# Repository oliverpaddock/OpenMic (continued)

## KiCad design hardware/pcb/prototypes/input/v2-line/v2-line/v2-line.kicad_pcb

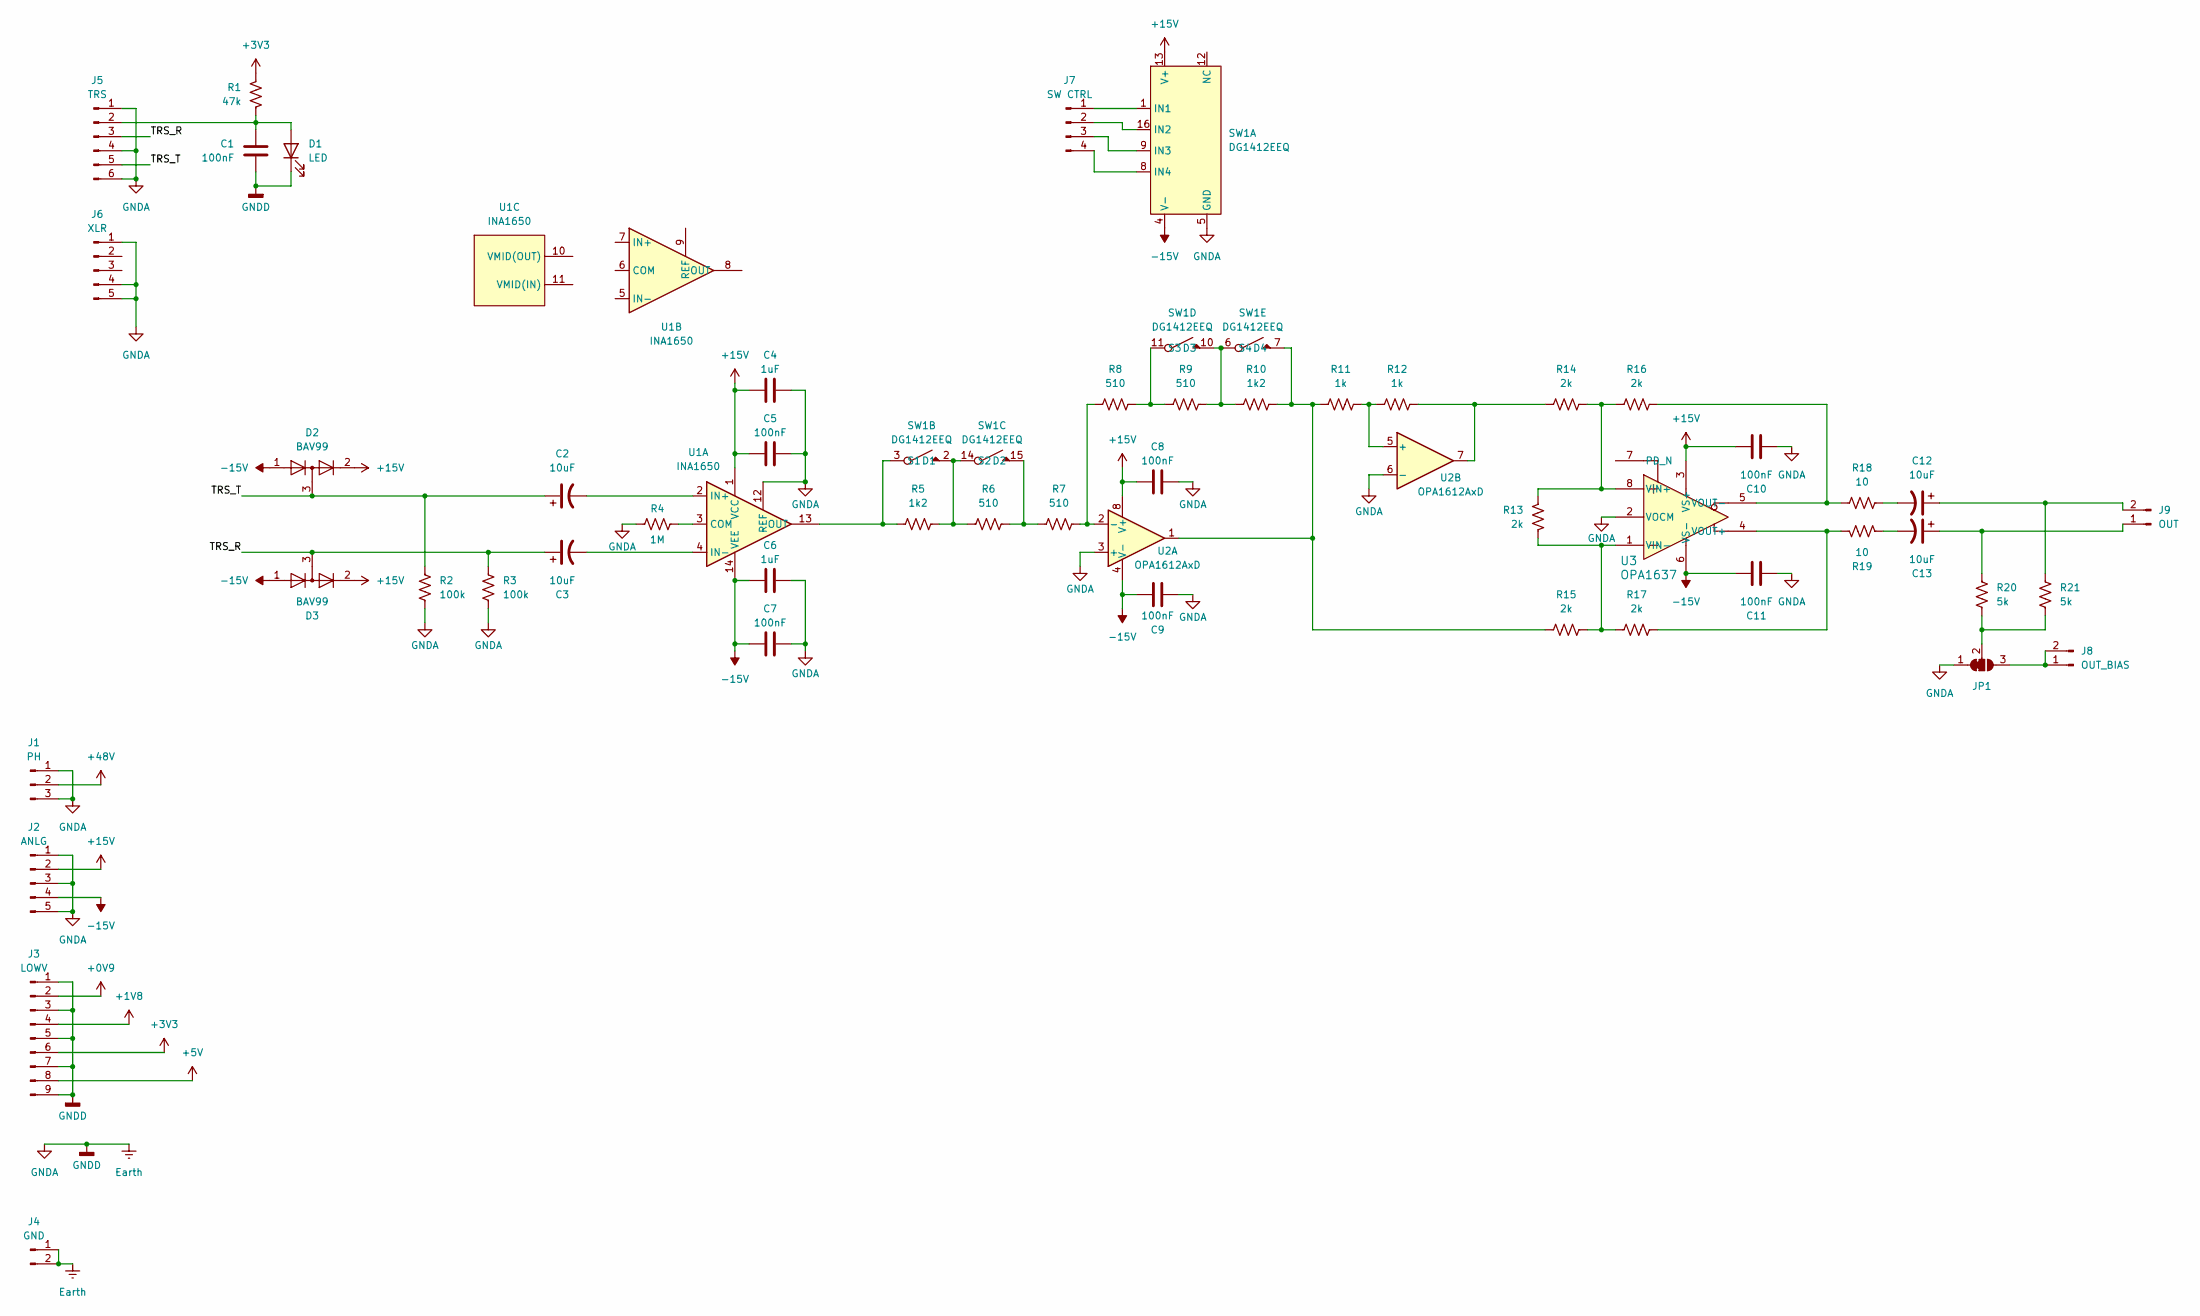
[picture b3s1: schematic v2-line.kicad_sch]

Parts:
C1, C10, C11: 100nF; C_0805_2012Metric_Pad1.18x1.45mm_HandSolder; Voltage 6
C2, C3, C12, C13: 10uF; C_Radial_D5.0mm_H11.0mm_P2.00mm; Voltage 50
C4, C6: 1uF; C_0805_2012Metric_Pad1.18x1.45mm_HandSolder; Voltage 50
C5, C7, C8, C9: 100nF; C_0805_2012Metric_Pad1.18x1.45mm_HandSolder; Voltage 50
D1: LED; LED_0805_2012Metric_Pad1.15x1.40mm_HandSolder
D2, D3: BAV99; SOT-23
J1: PH; PinHeader_1x03_P2.54mm_Vertical
J2: ANLG; PinHeader_1x05_P2.54mm_Vertical
J3: LOWV; PinHeader_1x09_P2.54mm_Vertical
J4: GND; PinHeader_1x02_P2.54mm_Vertical
J5: TRS; PinHeader_1x06_P2.54mm_Vertical
J6: XLR; PinHeader_1x05_P2.54mm_Vertical
J7: SW CTRL; PinHeader_1x04_P2.54mm_Vertical
J8: OUT_BIAS; PinHeader_1x02_P2.54mm_Vertical
J9: OUT; PinHeader_1x02_P2.54mm_Vertical
JP1: SolderJumper_3_Bridged12; SolderJumper-3_P1.3mm_Bridged12_RoundedPad1.0x1.5mm
R1: 47k; R_0805_2012Metric_Pad1.20x1.40mm_HandSolder
R2, R3: 100k; R_0805_2012Metric_Pad1.20x1.40mm_HandSolder
R4: 1M; R_0805_2012Metric_Pad1.20x1.40mm_HandSolder
R5, R10: 1k2; R_0805_2012Metric_Pad1.20x1.40mm_HandSolder
R6, R7, R8, R9: 510; R_0805_2012Metric_Pad1.20x1.40mm_HandSolder
R11, R12: 1k; R_0805_2012Metric_Pad1.20x1.40mm_HandSolder
R13, R14, R15, R16, R17: 2k; R_0805_2012Metric_Pad1.20x1.40mm_HandSolder
R18, R19: 10; R_0805_2012Metric_Pad1.20x1.40mm_HandSolder
R20, R21: 5k; R_0805_2012Metric_Pad1.20x1.40mm_HandSolder
SW1: DG1412EEQ; TSSOP-16_4.4x5mm_P0.65mm
U1: INA1650; TSSOP-14_4.4x5mm_P0.65mm
U2: OPA1612AxD; SOIC-8_3.9x4.9mm_P1.27mm
U3: OPA1637; VSSOP-8_3x3mm_P0.65mm

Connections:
+0V9: J3.2
+1V8: J3.4
+3V3: J3.6, R1.1
+5V: J3.8
+15V: C4.2, C5.2, C8.2, C10.1, D2.2 (A), D3.2 (A), J2.2, SW1.13 (V+), U1.1 (VCC), U2.8 (V+), U3.3 (VS+)
+48V: J1.2
-15V: C6.2, C7.2, C9.2, C11.1, D2.1 (K), D3.1 (K), J2.4, SW1.4 (V-), U1.14 (VEE), U2.4 (V-), U3.6 (VS-)
/TRS_R: C3.1, D3.3 (K), J5.3, R3.2
/TRS_T: C2.1, D2.3 (K), J5.5, R2.2
Earth: C1.2, C4.1, C5.1, C6.1, C7.1, C8.1, C9.1, C10.2, C11.2, D1.1 (K), J1.1, J1.3, J2.1, J2.3, J2.5, J3.1, J3.3, J3.5, J3.7, J3.9, J4.1, J4.2, J5.1, J5.4, J5.6, J6.1, J6.4, J6.5, JP1.1 (A), R2.1, R3.1, R4.1, SW1.5 (GND), U1.12 (REF), U2.3 (+), U2.6 (-), U3.2 (VOCM)
unnamed: C12.2, R18.2
unnamed: C13.2, R19.2
unnamed: C1.1, D1.2 (A), J5.2, R1.2
unnamed: J7.1, SW1.1 (IN1)
unnamed: J7.2, SW1.16 (IN2)
unnamed: J7.3, SW1.9 (IN3)
unnamed: J7.4, SW1.8 (IN4)
unnamed: J8.1, J8.2, JP1.3 (B)
unnamed: C13.1, J9.1, R20.2
unnamed: C12.1, J9.2, R21.2
unnamed: JP1.2 (C), R20.1, R21.1
unnamed: R12.1, R14.1, U2.7
unnamed: R5.1, R6.2, SW1.2 (D1), SW1.14 (S2)
unnamed: R5.2, SW1.3 (S1), U1.13 (OUT)
unnamed: R6.1, R7.2, SW1.15 (D2)
unnamed: R9.1, R10.2, SW1.6 (S4), SW1.10 (D3)
unnamed: R8.1, R9.2, SW1.11 (S3)
unnamed: R10.1, R11.2, R15.1, SW1.7 (D4), U2.1
unnamed: R4.2, U1.3 (COM)
unnamed: C2.2, U1.2 (IN+)
unnamed: C3.2, U1.4 (IN-)
unnamed: R7.1, R8.2, U2.2 (-)
unnamed: R11.1, R12.2, U2.5 (+)
unnamed: R13.2, R14.2, R16.1, U3.8 (VIN+)
unnamed: R13.1, R15.2, R17.1, U3.1 (VIN-)
unnamed: R17.2, R19.1, U3.4 (VOUT+)
unnamed: R16.2, R18.1, U3.5 (VOUT-)

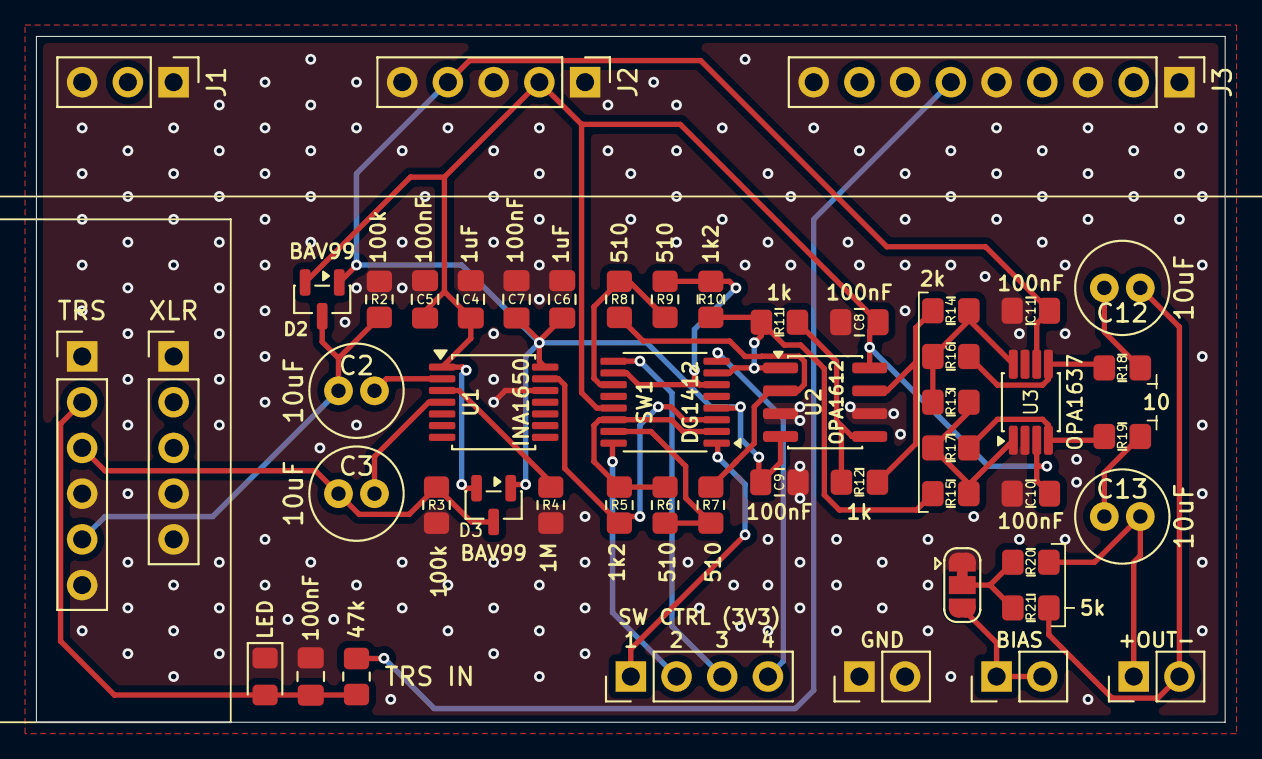
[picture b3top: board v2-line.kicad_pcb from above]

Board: 2 copper layers, 66.0 x 38.1 mm, 51 parts (0 on the bottom side), 33 nets.

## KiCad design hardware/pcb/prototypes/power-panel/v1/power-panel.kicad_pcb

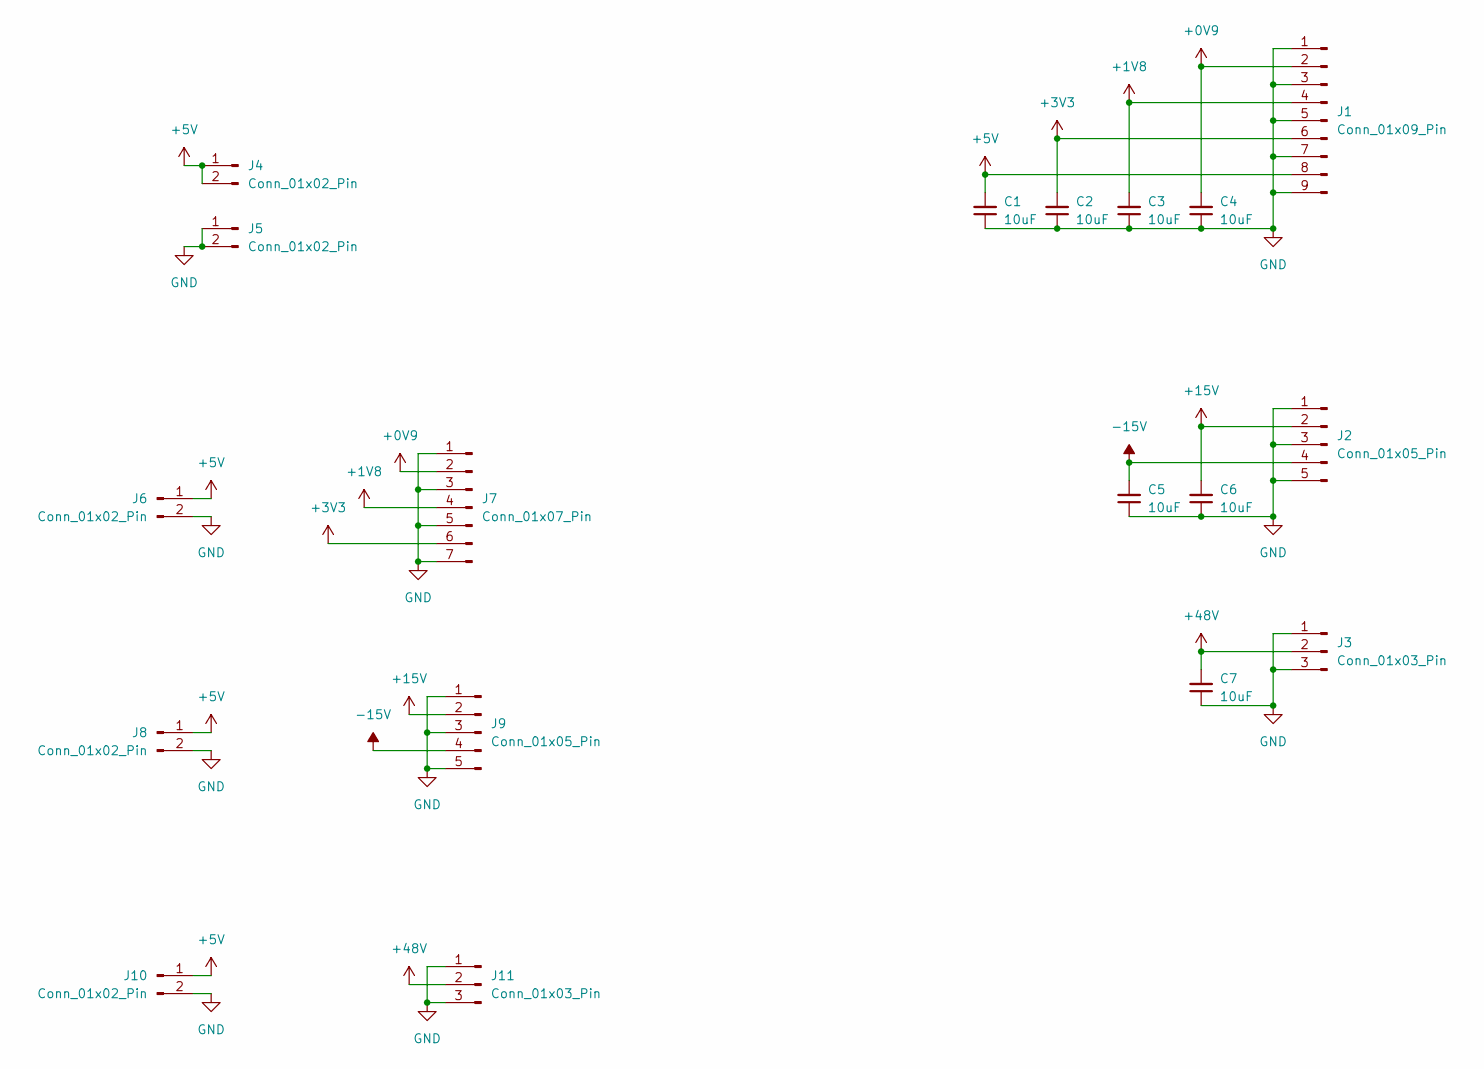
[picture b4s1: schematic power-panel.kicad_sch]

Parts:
C1, C2, C3, C4, C5, C6, C7: 10uF; C_0805_2012Metric_Pad1.18x1.45mm_HandSolder
J1: Conn_01x09_Pin; PinHeader_1x09_P2.54mm_Vertical
J2, J9: Conn_01x05_Pin; PinHeader_1x05_P2.54mm_Vertical
J3, J11: Conn_01x03_Pin; PinHeader_1x03_P2.54mm_Vertical
J4, J5, J6, J8, J10: Conn_01x02_Pin; PinHeader_1x02_P2.54mm_Vertical
J7: Conn_01x07_Pin; PinHeader_1x07_P2.54mm_Vertical

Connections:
+0V9: C4.2, J1.2, J7.2
+1V8: C3.2, J1.4, J7.4
+3V3: C2.2, J1.6, J7.6
+5V: C1.2, J1.8, J4.1, J4.2, J6.1, J8.1, J10.1
+15V: C6.2, J2.2, J9.2
+48V: C7.2, J3.2, J11.2
-15V: C5.2, J2.4, J9.4
GND: C1.1, C2.1, C3.1, C4.1, C5.1, C6.1, C7.1, J1.1, J1.3, J1.5, J1.7, J1.9, J2.1, J2.3, J2.5, J3.1, J3.3, J5.1, J5.2, J6.2, J7.1, J7.3, J7.5, J7.7, J8.2, J9.1, J9.3, J9.5, J10.2, J11.1, J11.3

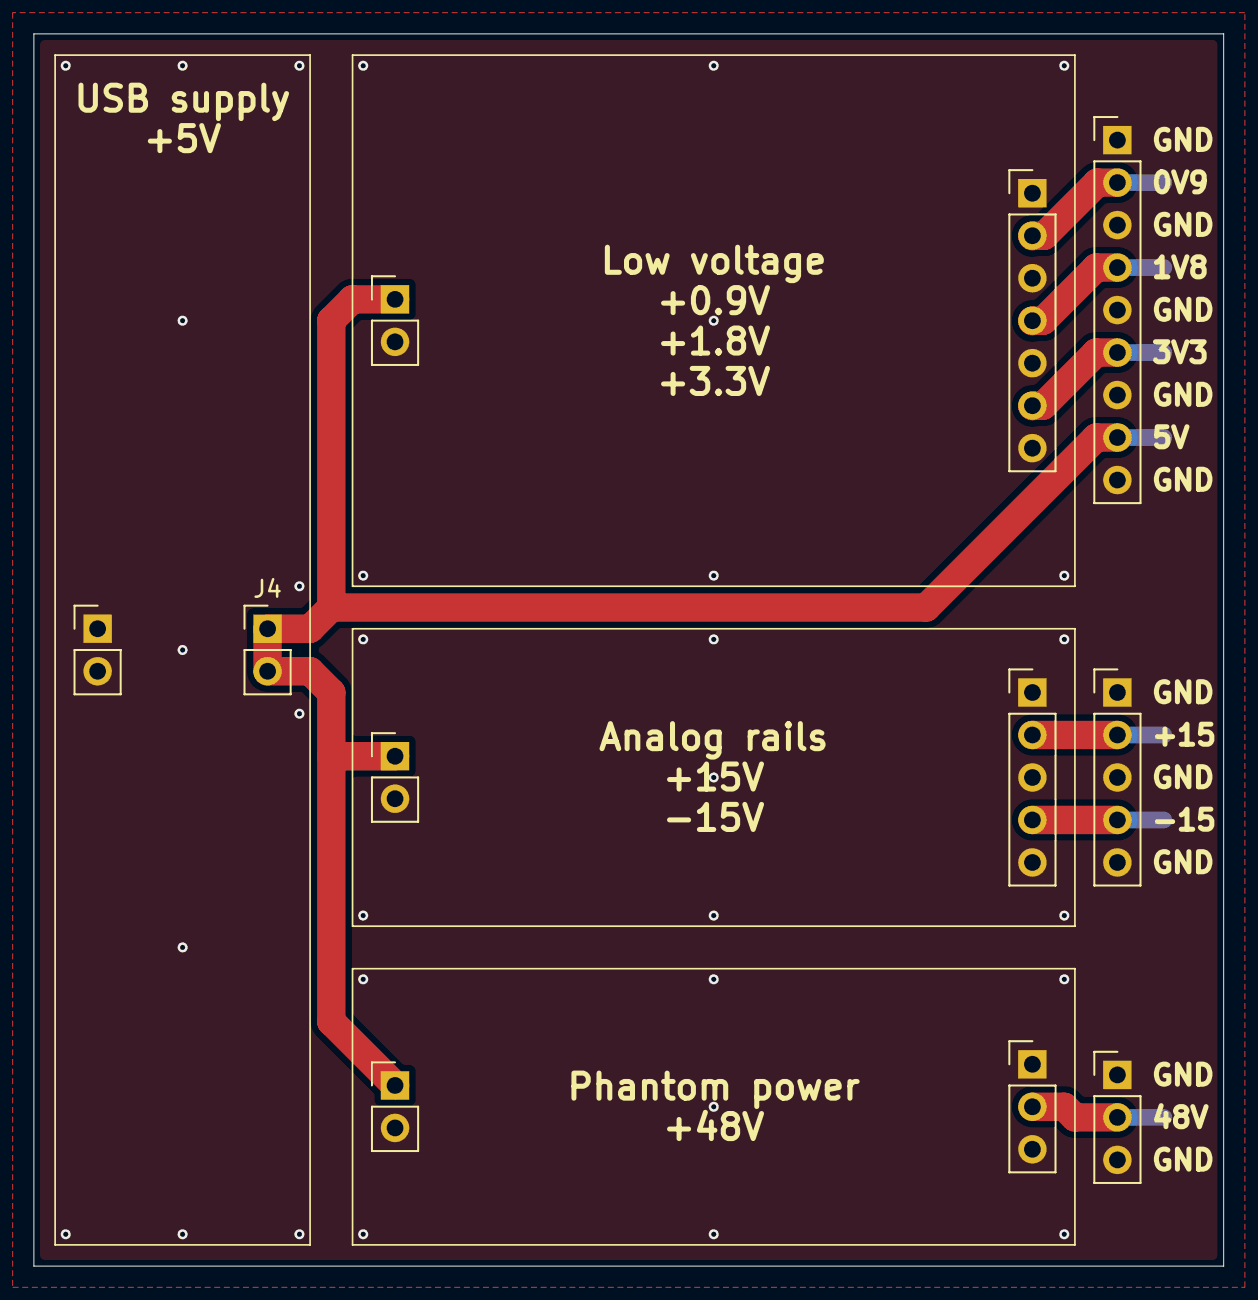
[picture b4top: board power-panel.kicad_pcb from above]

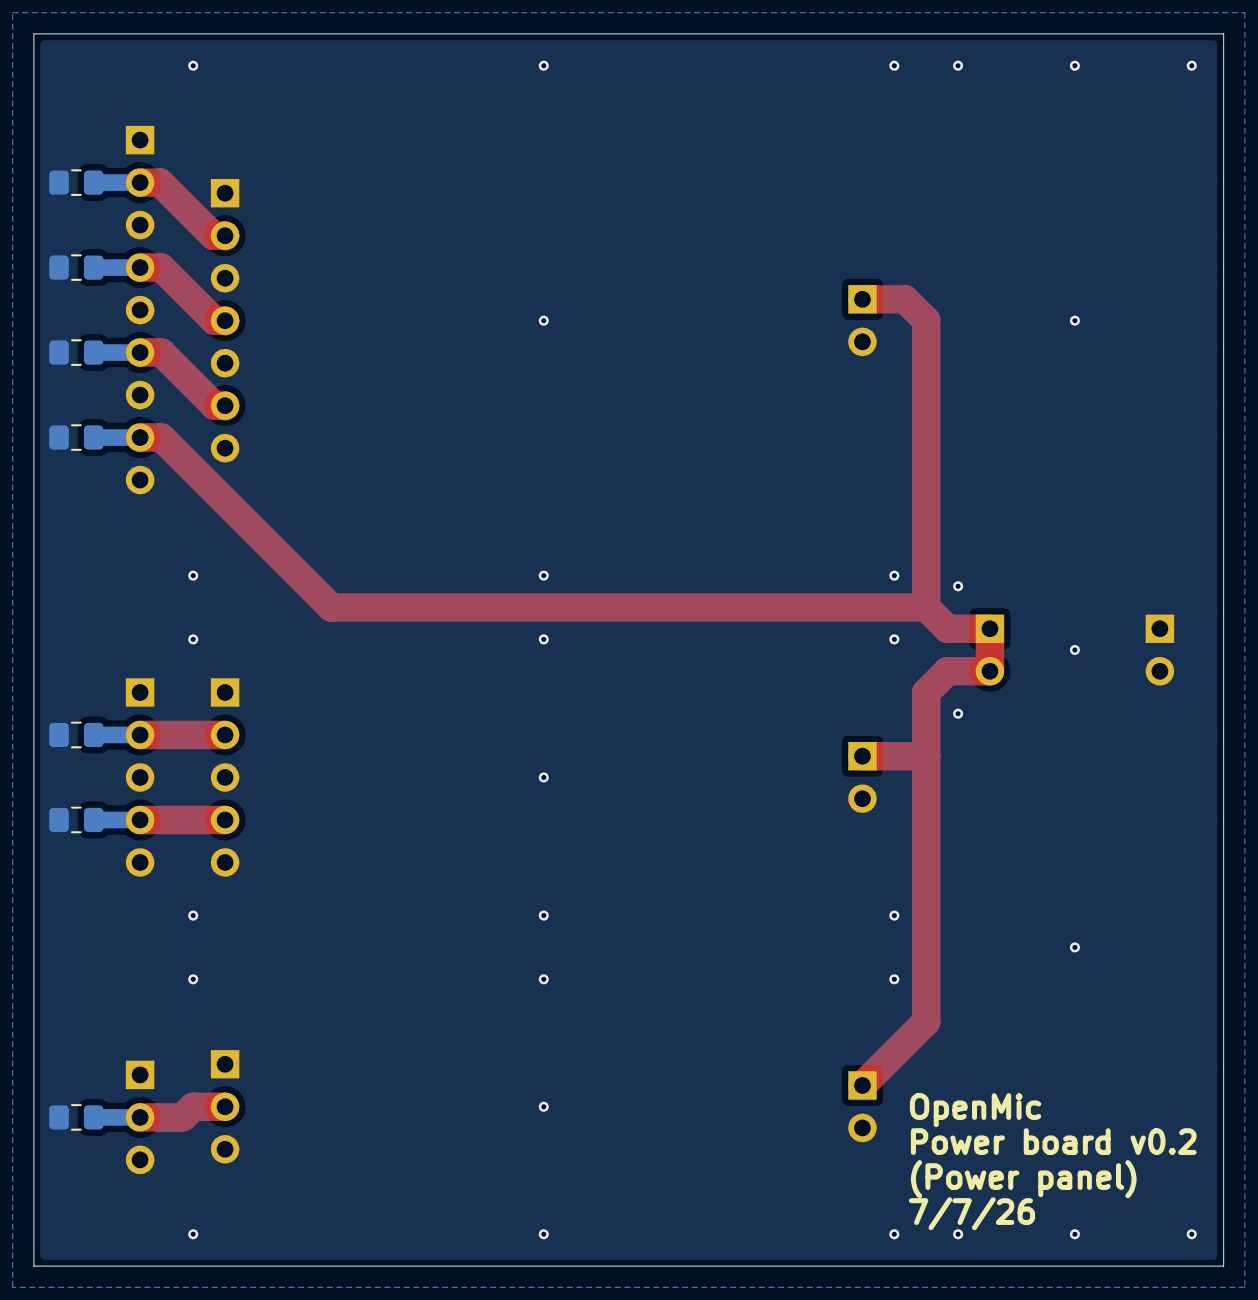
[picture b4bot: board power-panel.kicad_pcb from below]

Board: 2 copper layers, 71.1 x 73.7 mm, 18 parts (7 on the bottom side), 8 nets.

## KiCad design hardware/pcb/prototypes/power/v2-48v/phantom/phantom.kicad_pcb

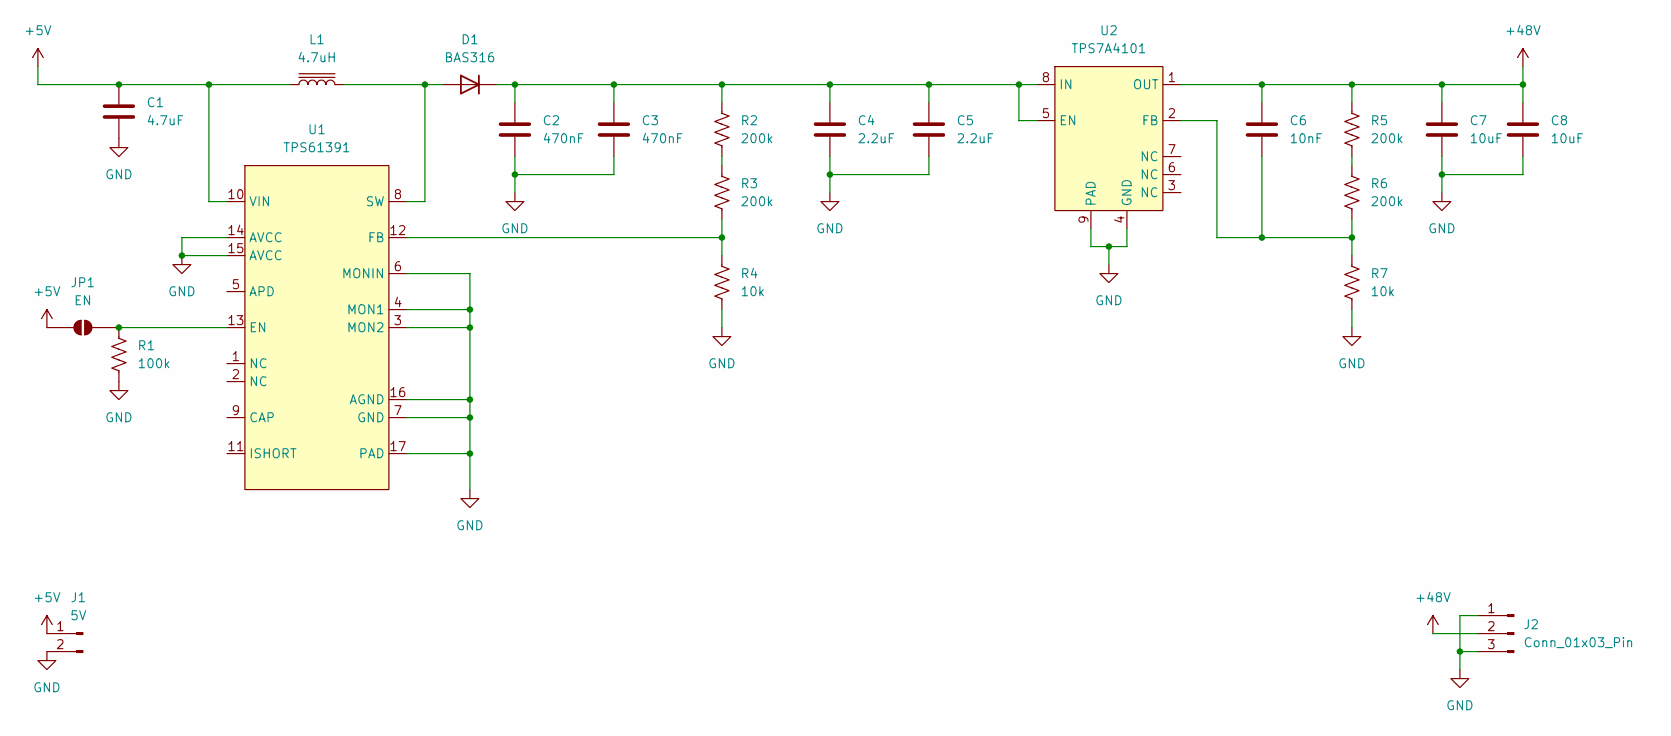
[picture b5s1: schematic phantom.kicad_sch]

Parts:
C1: 4.7uF; C_0805_2012Metric_Pad1.18x1.45mm_HandSolder; MPN CL21A475KAQNNNE; LCSC C1779
C2, C3: 470nF; C_0805_2012Metric_Pad1.18x1.45mm_HandSolder; MPN CL21B474KBFNNNE; LCSC C13967
C4, C5: 2.2uF; C_0805_2012Metric_Pad1.18x1.45mm_HandSolder; MPN CL21A225KBQNNNE; LCSC C377773
C6: 10nF; C_0805_2012Metric_Pad1.18x1.45mm_HandSolder; MPN CL21B103KBANNNC; LCSC C1710
C7, C8: 10uF; C_1210_3225Metric_Pad1.33x2.70mm_HandSolder; MPN CL21A106KAYNNNE; LCSC C15850
D1: BAS316; D_SOD-323; MPN BAS316; LCSC C8488
J1: 5V; PinHeader_1x02_P2.54mm_Vertical
J2: Conn_01x03_Pin; PinHeader_1x03_P2.54mm_Vertical
JP1: EN; SolderJumper-2_P1.3mm_Open_RoundedPad1.0x1.5mm
L1: 4.7uH; L_Wuerth_PMCI-201610; MPN DFE201612E-4R7M=P2; LCSC C3223763
R1: 100k; R_0805_2012Metric_Pad1.20x1.40mm_HandSolder; MPN 0805W8F1003T5E; LCSC C149504
R2, R3, R5, R6: 200k; R_0805_2012Metric_Pad1.20x1.40mm_HandSolder; MPN 0805W8F2003T5E; LCSC C17539
R4, R7: 10k; R_0805_2012Metric_Pad1.20x1.40mm_HandSolder; MPN 0805W8F1002T5E; LCSC C17414
U1: TPS61391; WQFN-16-1EP_3x3mm_P0.5mm_EP1.6x1.6mm; MPN TPS61391RTER; LCSC C1852151
U2: TPS7A4101; Texas_DGN0008B_VSSOP-8-1EP_3x3mm_P0.65mm_EP2x3mm_Mask1.88x1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; MPN TPS7A4101DGNR; LCSC C111739

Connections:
+5V: C1.1, J1.1, JP1.1 (A), L1.1, U1.10 (VIN)
+48V: C6.1, C7.1, C8.1, J2.2, R5.1, U2.1 (OUT)
GND: C1.2, C2.2, C3.2, C4.2, C5.2, C7.2, C8.2, J1.2, J2.1, J2.3, R1.2, R4.2, R7.2, U1.3 (MON2), U1.4 (MON1), U1.6 (MONIN), U1.7 (GND), U1.14 (AVCC), U1.15 (AVCC), U1.16 (AGND), U1.17 (PAD), U2.4 (GND), U2.9 (PAD)
unnamed: D1.2 (A), L1.2, U1.8 (SW)
unnamed: C2.1, C3.1, C4.1, C5.1, D1.1 (K), R2.1, U2.5 (EN), U2.8 (IN)
unnamed: JP1.2 (B), R1.1, U1.13 (EN)
unnamed: R2.2, R3.1
unnamed: R5.2, R6.1
unnamed: R3.2, R4.1, U1.12 (FB)
unnamed: C6.2, R6.2, R7.1, U2.2 (FB)

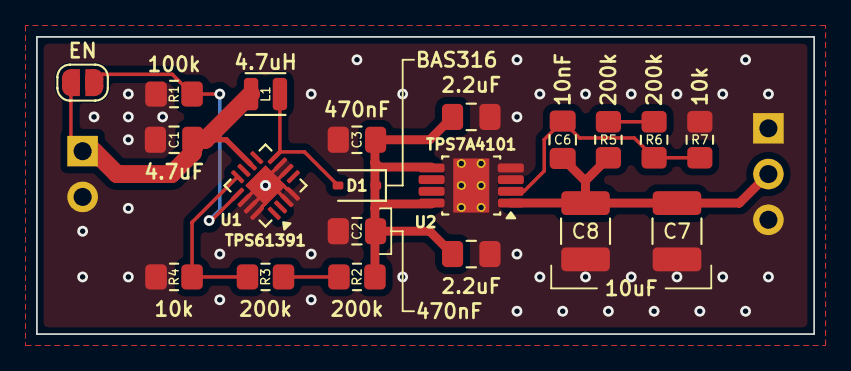
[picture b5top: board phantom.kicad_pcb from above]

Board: 2 copper layers, 43.2 x 16.5 mm, 22 parts (0 on the bottom side), 10 nets.

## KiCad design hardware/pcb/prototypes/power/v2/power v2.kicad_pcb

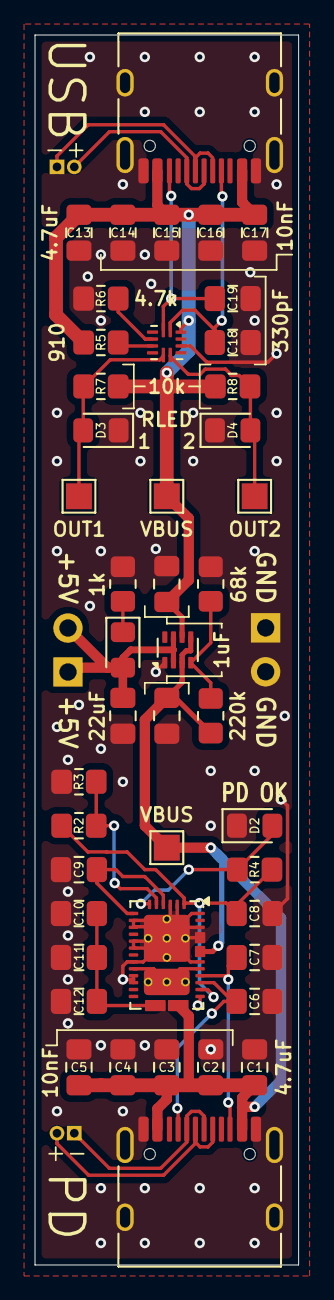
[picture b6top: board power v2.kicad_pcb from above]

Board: 2 copper layers, 15.2 x 71.1 mm, 49 parts (0 on the bottom side), 24 nets.

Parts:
C1, C9, C13: 4.7uF; C_0805_2012Metric_Pad1.18x1.45mm_HandSolder
C2, C3, C4, C5, C14, C15, C16, C17: 10nF; C_0805_2012Metric_Pad1.18x1.45mm_HandSolder
C6, C7, C18, C19: 330pF; C_0805_2012Metric_Pad1.18x1.45mm_HandSolder
C8, C12: 10uF; C_0805_2012Metric_Pad1.18x1.45mm_HandSolder
C10, C11, C22: 22uF; C_0805_2012Metric_Pad1.18x1.45mm_HandSolder
C20, C21: 1uF; C_0805_2012Metric_Pad1.18x1.45mm_HandSolder
D1, D2, D3, D4: R; LED_0805_2012Metric_Pad1.15x1.40mm_HandSolder
J1: 5V OUT; PinHeader_1x02_P2.54mm_Vertical
J2: USB_PD; USB_C_Receptacle_HRO_TYPE-C-31-M-12
J3, J5: D_PIN; PinHeader_1x02_P1.00mm_Vertical
J4: USB_C_Receptacle_USB2.0_16P; USB_C_Receptacle_HRO_TYPE-C-31-M-12
J6: GND; PinHeader_1x02_P2.54mm_Vertical
R1: 1k; R_0805_2012Metric_Pad1.20x1.40mm_HandSolder
R2: 180k; R_0805_2012Metric_Pad1.20x1.40mm_HandSolder
R3, R4, R7, R8: 10k; R_0805_2012Metric_Pad1.20x1.40mm_HandSolder
R5: 910; R_0805_2012Metric_Pad1.20x1.40mm_HandSolder
R6: 4.7k; R_0805_2012Metric_Pad1.20x1.40mm_HandSolder
R9: 220k; R_0805_2012Metric_Pad1.20x1.40mm_HandSolder
R10: 68k; R_0805_2012Metric_Pad1.20x1.40mm_HandSolder
TP1: VBUS_PD; TestPoint_Pad_1.5x1.5mm
TP2: VBUS_USB; TestPoint_Pad_1.5x1.5mm
TP3: OUT1; TestPoint_Pad_1.5x1.5mm
TP4: OUT2; TestPoint_Pad_1.5x1.5mm
U1: TPS25730AD; Texas_REF0038A_WQFN-38-2EP_6x4mm_P0.4
U2: TUSB321; Texas_X2QFN-12_1.6x1.6mm_P0.4mm
U3: TPS2116DRL; SOT-583-8

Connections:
+5V: C22.1, D1.2 (A), J1.1, J1.2, U3.2 (VOUT), U3.7 (VOUT)
/5V PD/ADCIN3: R2.2, R3.1, U1.5 (ADCIN3)
/5V PD/CC1_PD: C6.1, J2.A5 (CC1), U1.28 (CC1)
/5V PD/CC2_PD: C7.1, J2.B5 (CC2), U1.29 (CC2)
/5V PD/LDO_1V5: C9.1, U1.4 (LDO_1V5), U1.7 (ADCIN4)
/5V PD/LDO_3V3: C8.1, R2.1, R4.2, U1.1 (LDO_3V3), U1.27 (PD5VMAX)
/5V PD/PPHV: C10.1, C11.1, C12.1, U1.20 (PPHV)
/5V PD/VBUS_PD: C1.1, C2.1, C3.1, C4.1, C5.1, C20.1, J2.A4 (VBUS), J2.A9 (VBUS), J2.B4 (VBUS), J2.B9 (VBUS), R9.1, TP1.1 (1_1), U1.23 (VBUS_IN), U1.32 (VBUS), U3.3 (VIN1), U3.5 (MODE)
/5V USB/CC1_USB: C18.1, J4.A5 (CC1), U2.1 (CC1)
/5V USB/CC2_USB: C19.1, J4.B5 (CC2), U2.2 (CC2)
/5V USB/VBUS_USB: C13.1, C14.1, C15.1, C16.1, C17.1, C21.1, J4.A4 (VBUS), J4.A9 (VBUS), J4.B4 (VBUS), J4.B9 (VBUS), R5.1, R7.2, R8.2, TP2.1 (1_1), U2.12 (VDD), U3.6 (VIN2)
/Input Selector/PR1: R9.2, R10.1, U3.4 (PR1)
GND: C1.2, C2.2, C3.2, C4.2, C5.2, C6.2, C7.2, C8.2, C9.2, C10.2, C11.2, C12.2, C13.2, C14.2, C15.2, C16.2, C17.2, C18.2, C19.2, C20.2, C21.2, C22.2, D2.1 (K), D3.1 (K), D4.1 (K), J2.A1 (GND), J2.A12 (GND), J2.B1 (GND), J2.B12 (GND), J2.SH (SHIELD), J4.A1 (GND), J4.A12 (GND), J4.B1 (GND), J4.B12 (GND), J4.SH (SHIELD), J6.1, J6.2, R1.2, R3.2, R6.1, R10.2, U1.2 (ADCIN1), U1.3 (ADCIN2), U1.8 (I2Ct_SDA), U1.9 (I2Ct_SCL), U1.11 (GND), U1.12 (GND), U1.14 (GND), U1.16 (GND), U1.17 (GND), U1.26 (RESERVED), U1.31 (GND), U1.34 (GND), U1.36 (RESERVED), U1.38 (VIN_3V3), U1.39 (GND), U2.10 (GND), U3.1 (GND)
unnamed: D1.1 (K), R1.1
unnamed: D2.2 (A), R4.1, U1.6 (CAP_MIS)
unnamed: D3.2 (A), R7.1, TP3.1 (1_1), U2.7 (OUT1)
unnamed: D4.2 (A), R8.1, TP4.1 (1_1), U2.8 (OUT2)
unnamed: J2.A7 (D-), J2.B7 (D-), J3.1
unnamed: J2.A6 (D+), J2.B6 (D+), J3.2
unnamed: J4.A7 (D-), J4.B7 (D-), J5.1
unnamed: J4.A6 (D+), J4.B6 (D+), J5.2
unnamed: U1.15 (DRAIN), U1.30 (DRAIN), U1.40 (DRAIN)
unnamed: R6.2, U2.4 (PORT)
unnamed: R5.2, U2.5 (VBUS_DET)
